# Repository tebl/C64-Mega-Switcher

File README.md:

# C64 Mega Switcher

With 8bitdo starting recent productions of new quality wireless controllers for the Sega Mega Drive/Genesis, I thought it was time to look into adapting the usage of these with the Commodore 64. Normally a controller of this type would be HARMFUL to your C64 WITHOUT using of a suitable adapter, a great one was made by SukkoPera a while back and I've taken a lot of inspiration as well as lifting a couple of the kicad footprints from his [OpenC64MegaDrivePadAdapter](https://github.com/SukkoPera/OpenC64MegaDrivePadAdapter). What this project aims to add into the mix is a way of swapping the active port your joystick is connected to at the press of a button, that way you don't have to fiddle around with cables every time you try out a game that for some reason insists on having the joystick in the other port!

I could probably have made one that was a lot smaller by using SMD, or possibly even a lot more dynamic one by the use of an AVR at it's core, but I wanted one that was easy to build and does not require any other skills than pointing the hot end of a soldering iron to the requisite parts. Hopefully it'll be something anyone can build and have fun with!

## Building the switcher
Soldering together the few components should be easy going as long as you have access to reasonable tools, personally I'm using a cheap soldering station with adjustable temperature so no need to go expensive if you don't have to. Use 60/40 soldering tin, the lead free makes to job a lot harder if you're new to the hobby.

Start by studying the PCB, both sides and perform dry fits to see that you have an idea of where everything goes since removing things is always a lot harder than getting it right in the first place (match orientation to symbols, see gallery images for reference if you're unsure). The diodes are installed standing, the stripe goes into the board so that it is laying directly against the board - a hint for making these look pretty, is wrapping one of the wires around a small screwdriver to get the loops looking almost identical!

The female DB9 connectors used for port 1/2 comes with a metal shroud, this comes off when you remove the two screws that would be in the way anyway. Given that the C64 ports are made out of plastic, the metal shroud is not needed though you could possibly keep it by gluing it to the connector if you really wanted to and then filling in the screw holes with solder to keep them together afterwards. Do a testfit of the connectors with the C64 before soldering them to the board, this is recommended in order to avoid adding any stress to the C64 board, usually I keep the metal anchors as they keep the connector from wriggling around too much.

I recommend putting something underneath the board, so that it isn't flexing too much when pressing the buttons. Nylon standoffs cut to size, extreme amounts of layered tape - you decide what works best for you and whatever leftovers you can find in the parts-bin!

## Using the switcher
Firmly insert the switcher into the C64, making sure that it is inserted the whole way and fits firmly without feeling loose. When playing a game, if you encounter a game that expects a joystick inserted into the other port, just press the button for the port you want to use instead. The module supports alternate fire, in other words the second button that was found on the ill-fated Commodore 64 Games System console - this works, but I've so far only tested it with Robocop 2 on cartridge.

**WARNING!**
 - Do **NOT** move any of the jumpers while the computer is switched on, doing so may cause damage to it. Always power off first!
 - Do **NOT** jumper so that more than one button/direction does the same thing, for example: if you jumper the B button for UP, then you have to REMOVE the jumper enabling D-PAD UP!
 - In essence, just make sure to only jumper once per vertical or horizontal line of jumpers. Personally I use C as the primary fire button, B is jumpered as alternate fire for the few titles that support secondary fire buttons. If in doubt, refer to the image at the top.

# Schematic
The supplied KiCad files should be sufficient as both a schematic and as a  starting point for ordering PCBs (basically you could just zip the contents of the export folder and upload that on a fabrication site), the schematic is also available in [PDF-format](https://github.com/tebl/C64-Mega-Switcher/blob/master/export/C64%20Mega%20Switcher.pdf) and this is what you'll need to print and work your way through this things don't work as expected after assembly.

# BOM
Most parts should be easy to get a hold of from your favourite local electronic component shop, but given that I don't have access to such shops where I live so everything was based on whatever I could get cheapest from ebay/AliExpress (free shipping, plan on usually waiting 3-4 weeks though). Parts listed in parenthesis are optional and is only used for the secondary fire button, so you can safely skip these unless you want the whole thing built in one go (BC547 can be substituted with a 2N2222 connected the wrong way around).

| Reference    | Item                                  | Count |
| ------------ | ------------------------------------- | ----- |
| PCB          | Fabricate using Gerber files ([order](https://www.pcbway.com/project/shareproject/Commodore_64_Mega_Switcher__Revision_B_.html?inviteid=88707))          |     1 |
| C1-C3        | 100nF capacitor                       |     3 |
| D1,D2        | 5mm LED                               |     2 |
| D3-D12       | 1N4148 diode                          |    10 |
| R1,R2        | 10k ohm resistor                      |     2 | 
| R3,R4        | 220 ohm resistor                      |     2 |
| R5,R7        | 2k2 ohm resistor                      |   (2) |
| R6           | 100k ohm resistor                     |   (1) |
| Q1           | BC547 TO-92 transistor                |   (1) |
| U1           | 74HCT4053 or CD4053 DIP-16            |     2 |
| U3           | NE555 DIP-8                           |     1 |
| SW1,SW2      | SPST momentary push button            |     2 |
| JP1          | 2-pin straight header                 |     1 |
| J1,J2        | Female DB9 right-angle connector      |     2 |
| J3           | Male DB9 right-angle connector        |     1 |
| J4,J5        | 2x2-pin straight header               |     2 |

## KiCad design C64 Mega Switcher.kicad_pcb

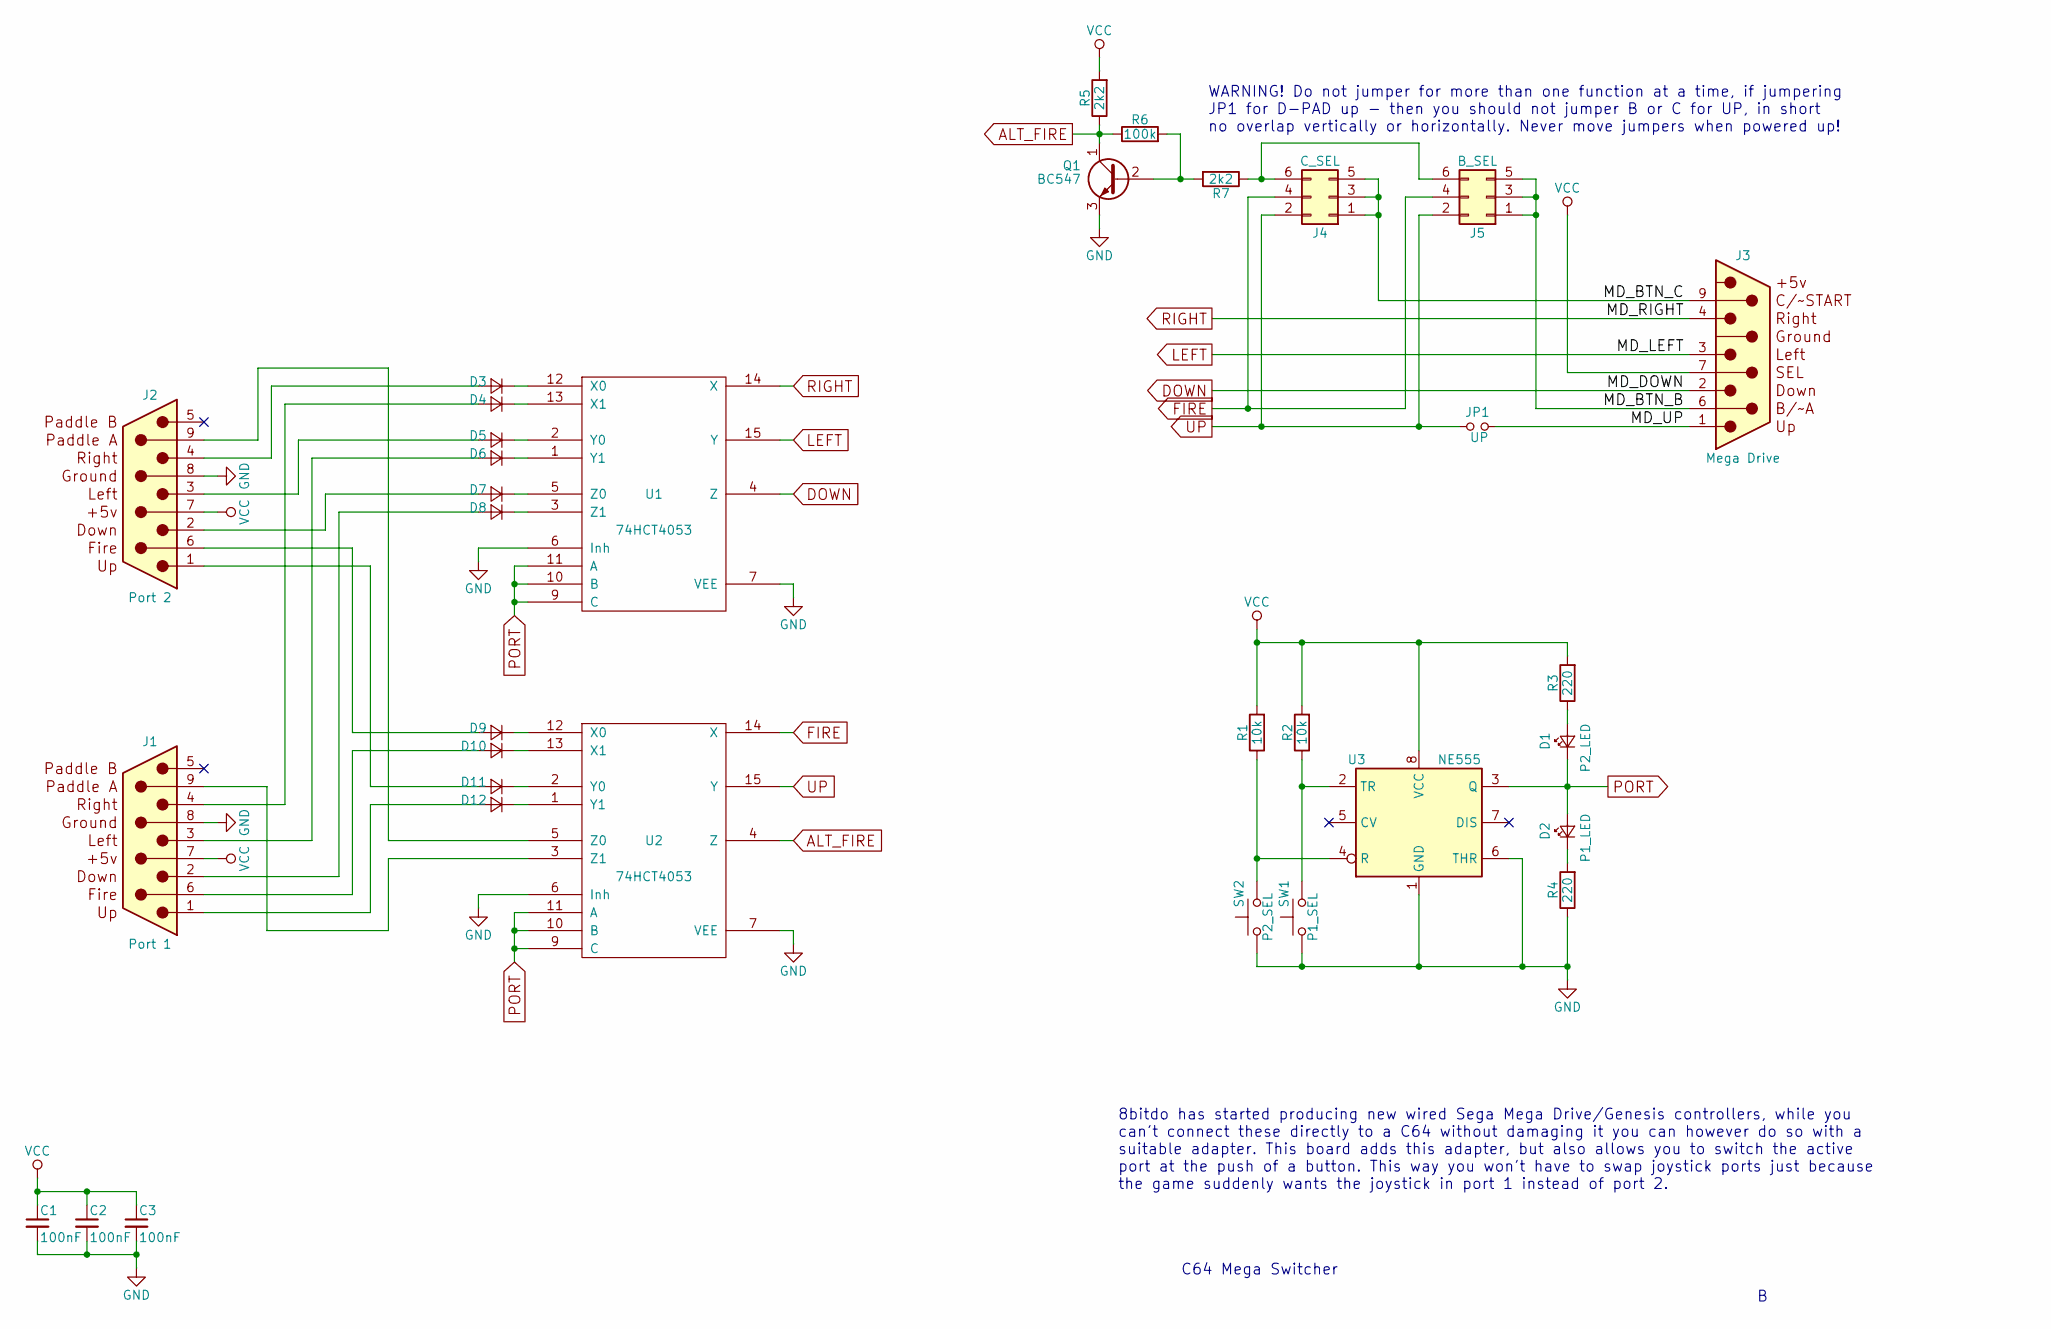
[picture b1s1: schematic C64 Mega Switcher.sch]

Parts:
C1, C2, C3: 100nF; C_Disc_D4.7mm_W2.5mm_P5.00mm
D1: P2_LED; LED_D5.0mm
D2: P1_LED; LED_D5.0mm
D3, D4, D5, D6, D7, D8, D9, D10, D11, D12: 1N4148; D_DO-35_SOD27_P2.54mm_Vertical_AnodeUp
J1: Port 1; DSUB-9_Female_Horizontal_P2.77x2.84mm_EdgePinOffset7.70mm_H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
J2: Port 2; DSUB-9_Female_Horizontal_P2.77x2.84mm_EdgePinOffset7.70mm_H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
J3: Mega Drive; DSUB-9_Male_Horizontal_P2.77x2.84mm_EdgePinOffset7.70mm_Hou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
J4: C_SEL; Pin_Header_Straight_2x03_Pitch2.54mm
J5: B_SEL; Pin_Header_Straight_2x03_Pitch2.54mm
JP1: UP; Pin_Header_Straight_1x02_Pitch2.54mm
Q1: BC547; TO-92_Inline_Wide
R1, R2: 10k; R_Axial_DIN0207_L6.3mm_D2.5mm_P10.16mm_Horizontal
R3, R4: 220; R_Axial_DIN0207_L6.3mm_D2.5mm_P10.16mm_Horizontal
R5, R7: 2k2; R_Axial_DIN0207_L6.3mm_D2.5mm_P10.16mm_Horizontal
R6: 100k; R_Axial_DIN0207_L6.3mm_D2.5mm_P10.16mm_Horizontal
SW1: P1_SEL; SW_PUSH_6mm
SW2: P2_SEL; SW_PUSH_6mm
U1, U2: 74HCT4053; DIP-16_W7.62mm_Socket
U3: NE555; DIP-8_W7.62mm_Socket

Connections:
/MD_BTN_B: J3.6, J5.1, J5.3, J5.5
/MD_BTN_C: J3.9, J4.1, J4.3, J4.5
/MD_UP: J3.1, JP1.2
ALT_FIRE: Q1.1 (C), R5.1, R6.1, U2.4 (Z)
DOWN: J3.2, U1.4 (Z)
FIRE: J4.4, J5.4, U2.14 (X)
GND: C1.2, C2.2, C3.2, J1.8 (GND), J2.8 (GND), J3.8 (GND), Q1.3 (E), R4.1, SW1.1, SW2.1, U1.6 (Inh), U1.7 (VEE), U1.8 (GND), U2.6 (Inh), U2.7 (VEE), U2.8 (GND), U3.1 (GND), U3.6 (THR)
LEFT: J3.3, U1.15 (Y)
unnamed: D1.2 (A), R3.1
unnamed: D2.1 (K), R4.2
unnamed: D3.1 (K), U1.12 (X0)
unnamed: D3.2 (A), J2.4
unnamed: D4.1 (K), U1.13 (X1)
unnamed: D4.2 (A), J1.4
unnamed: D5.1 (K), U1.2 (Y0)
unnamed: D5.2 (A), J2.3
unnamed: D6.1 (K), U1.1 (Y1)
unnamed: D6.2 (A), J1.3
unnamed: D7.1 (K), U1.5 (Z0)
unnamed: D7.2 (A), J2.2
unnamed: D8.1 (K), U1.3 (Z1)
unnamed: D8.2 (A), J1.2
unnamed: D9.1 (K), U2.12 (X0)
unnamed: D9.2 (A), J2.6
unnamed: D10.1 (K), U2.13 (X1)
unnamed: D10.2 (A), J1.6
unnamed: D11.1 (K), U2.2 (Y0)
unnamed: D11.2 (A), J2.1
unnamed: D12.1 (K), U2.1 (Y1)
unnamed: D12.2 (A), J1.1
unnamed: J1.9, U2.3 (Z1)
unnamed: J2.9, U2.5 (Z0)
unnamed: J4.6, J5.6, R7.1
unnamed: Q1.2 (B), R6.2, R7.2
unnamed: R1.1, SW2.2, U3.4 (R)
unnamed: R2.1, SW1.2, U3.2 (TR)
PORT: D1.1 (K), D2.2 (A), U1.9 (C), U1.10 (B), U1.11 (A), U2.9 (C), U2.10 (B), U2.11 (A), U3.3 (Q)
RIGHT: J3.4, U1.14 (X)
UP: J4.2, J5.2, JP1.1, U2.15 (Y)
VCC: C1.1, C2.1, C3.1, J1.7 (VCC), J2.7 (VCC), J3.5 (VCC), J3.7, R1.2, R2.2, R3.2, R5.2, U1.16 (VCC), U2.16 (VCC), U3.8 (VCC)

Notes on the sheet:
C64 Mega Switcher
8bitdo has started producing new wired Sega Mega Drive/Genesis controllers, while you can't connect these directly to a C64 without damaging it you can however do so with a suitable adapter. This board adds this adapter, but also allows you to switch the active port at the push of a button. This wa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
WARNING! Do not jumper for more than one function at a time, if jumpering JP1 for D-PAD up - then you should not jumper B or C for UP, in short no overlap vertically or horizontally. Never move jumpers when powered up!

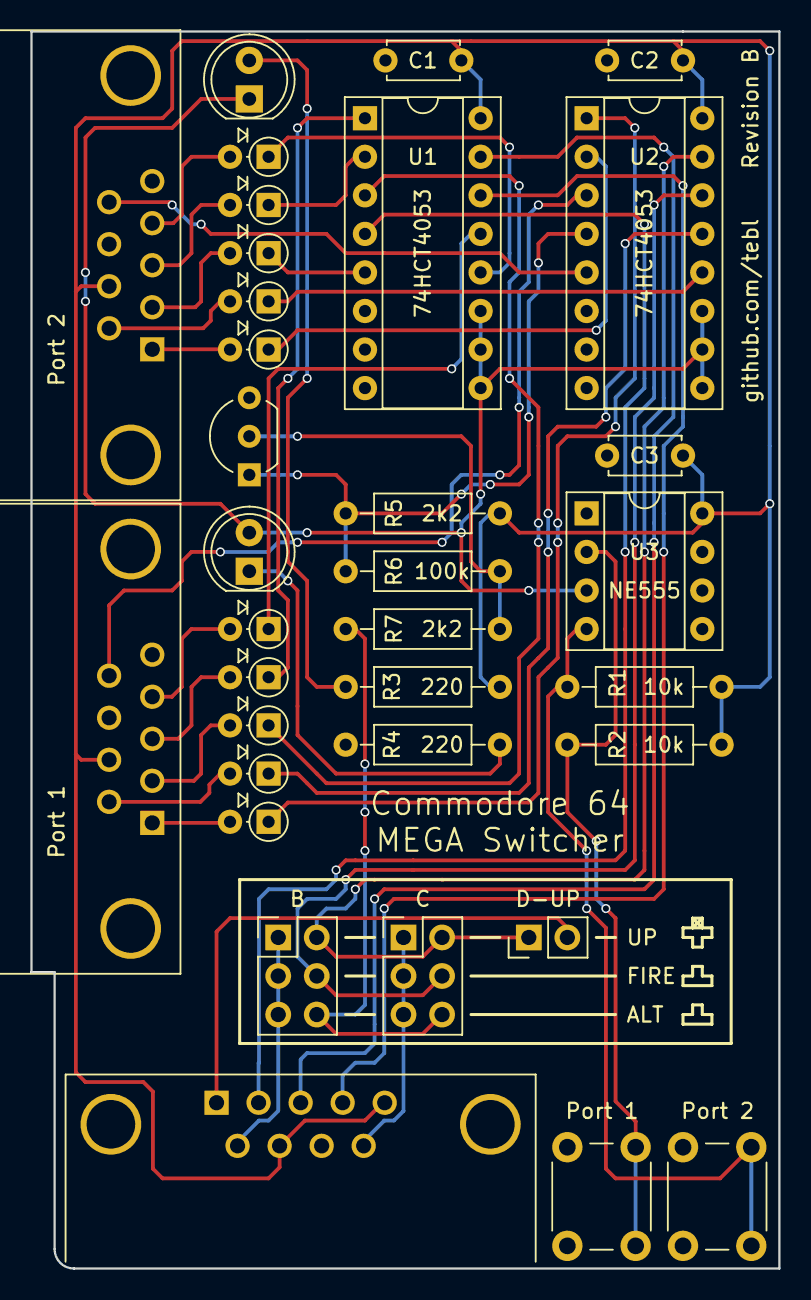
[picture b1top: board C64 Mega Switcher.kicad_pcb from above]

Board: 2 copper layers, 49.3 x 81.5 mm, 34 parts (0 on the bottom side), 40 nets.

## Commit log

2019-06-24 Added measurement pictures
2019-06-24 Mapped single port in schematic
2019-06-24 Added joystick switcher and assigned footprints.
2019-06-24 Fixed schematic validations
2019-06-25 General part placement
2019-06-25 Routed nets and added silkscreen text
2019-06-25 Gerber export
2019-06-26 Added protection diodes
2019-07-30 Swapped buttons the right way
2019-07-30 Added tracks to buttons
2019-07-31 Added silkscreen warnings
2019-07-31 Added README
2019-07-31 Fixed link
2019-09-06 Updated PCB with ALT-FIRE, assigned new footprints
2019-09-26 Added gallery images
2019-09-26 Revision B
2019-09-26 Updated BOM
2019-09-28 Fixed PDF link

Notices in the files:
C64 Mega Switcher.kicad_pcb:
Licensed under
CERN OHL v.1.2
